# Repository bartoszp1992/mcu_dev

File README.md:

# MCU DEV G071KBT 

- STM32G071KBT 
- 2x 1117 (3V3, 5V)
- kwarc zegarkowy. 
- GPIO
- SWD
- 2x LED (power, GPIO).

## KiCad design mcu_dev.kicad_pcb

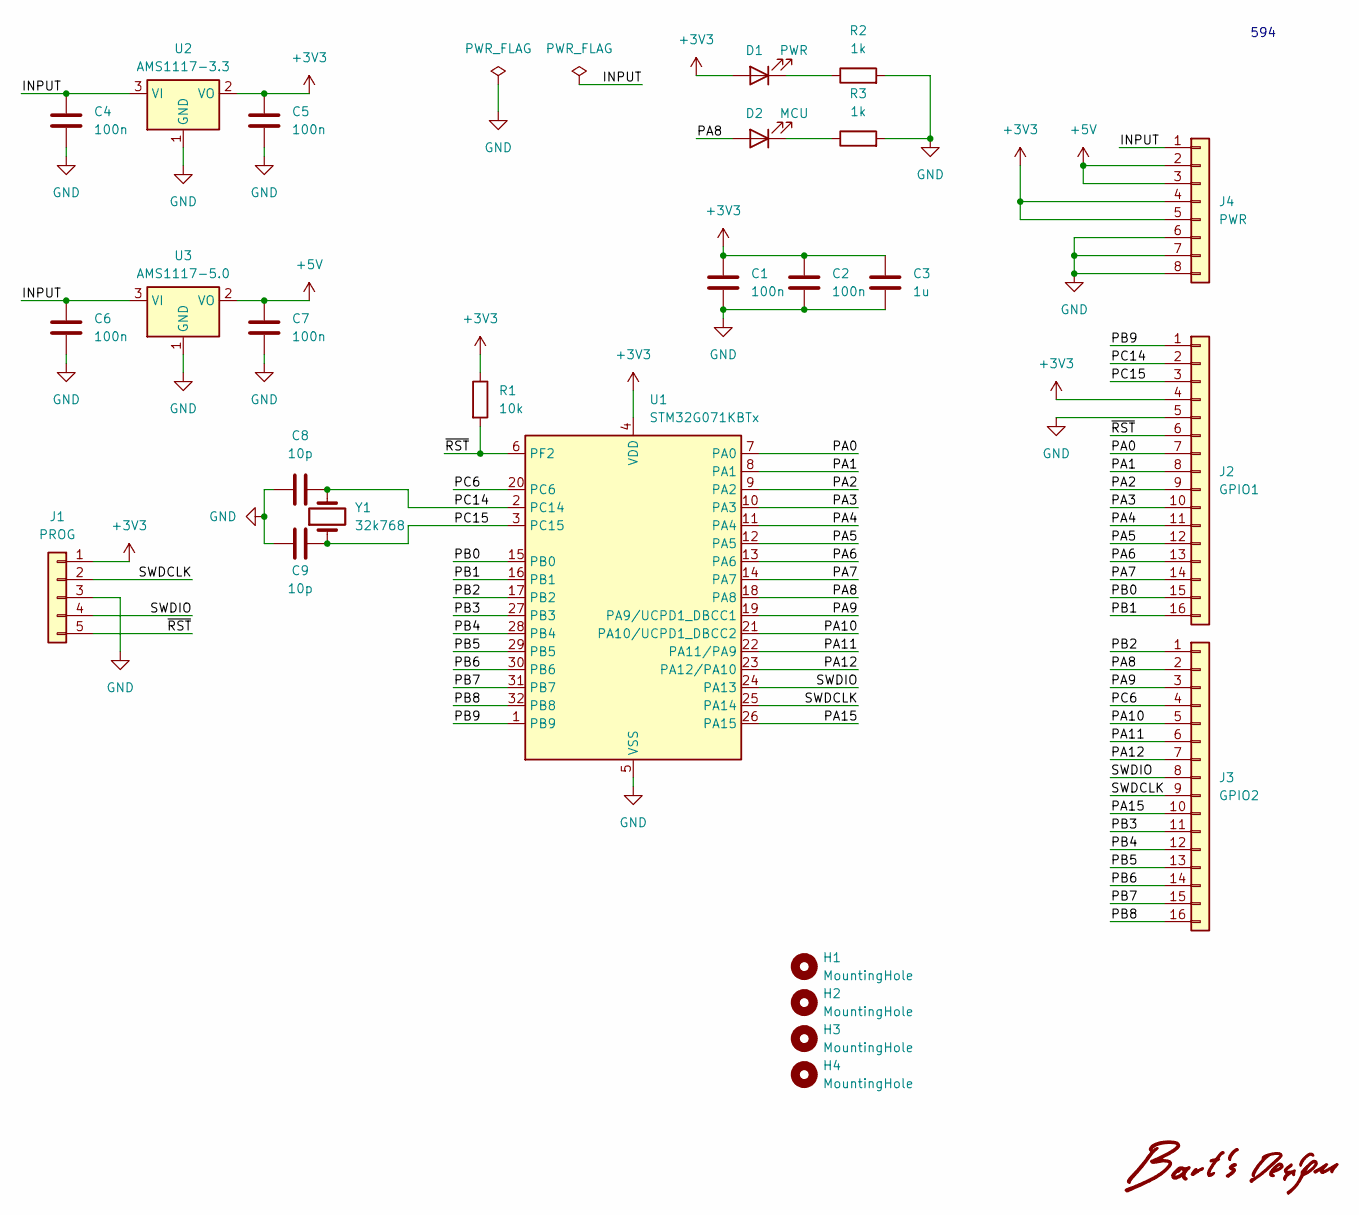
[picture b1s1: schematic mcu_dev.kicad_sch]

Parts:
C1, C2, C4, C5, C6, C7: 100n; C_0603_1608Metric
C3: 1u; C_0603_1608Metric
C8, C9: 10p; C_0603_1608Metric
D1: PWR; LED_0603_1608Metric
D2: MCU; LED_0603_1608Metric
H1, H2, H3, H4: MountingHole; MountingHole_3.2mm_M3
J1: PROG; PinSocket_1x05_P2.54mm_Vertical
J2: GPIO1; PinSocket_1x16_P2.54mm_Vertical
J3: GPIO2; PinSocket_1x16_P2.54mm_Vertical
J4: PWR; PinSocket_1x08_P2.54mm_Vertical
Logo1: Barts Design
R1: 10k; R_0603_1608Metric
R2, R3: 1k; R_0603_1608Metric
U1: STM32G071KBTx; LQFP-32_7x7mm_P0.8mm
U2: AMS1117-3.3; SOT-223-3_TabPin2
U3: AMS1117-5.0; SOT-223-3_TabPin2
Y1: 32k768; Crystal_AT310_D3.0mm_L10.0mm_Horizontal

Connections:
+3V3: C1.1, C2.1, C3.1, C5.1, D1.2 (A), J1.1, J2.4, J4.4, J4.5, R1.1, U1.4 (VDD), U2.2 (VO)
+5V: C7.1, J4.2, J4.3, U3.2 (VO)
/INPUT: C4.1, C6.1, J4.1, U2.3 (VI), U3.3 (VI)
/PA0: J2.7, U1.7 (PA0)
/PA1: J2.8, U1.8 (PA1)
/PA2: J2.9, U1.9 (PA2)
/PA3: J2.10, U1.10 (PA3)
/PA4: J2.11, U1.11 (PA4)
/PA5: J2.12, U1.12 (PA5)
/PA6: J2.13, U1.13 (PA6)
/PA7: J2.14, U1.14 (PA7)
/PA8: D2.2 (A), J3.2, U1.18 (PA8)
/PA9: J3.3, U1.19 (PA9/UCPD1_DBCC1)
/PA10: J3.5, U1.21 (PA10/UCPD1_DBCC2)
/PA11: J3.6, U1.22 (PA11/PA9)
/PA12: J3.7, U1.23 (PA12/PA10)
/PA15: J3.10, U1.26 (PA15)
/PB0: J2.15, U1.15 (PB0)
/PB1: J2.16, U1.16 (PB1)
/PB2: J3.1, U1.17 (PB2)
/PB3: J3.11, U1.27 (PB3)
/PB4: J3.12, U1.28 (PB4)
/PB5: J3.13, U1.29 (PB5)
/PB6: J3.14, U1.30 (PB6)
/PB7: J3.15, U1.31 (PB7)
/PB8: J3.16, U1.32 (PB8)
/PB9: J2.1, U1.1 (PB9)
/PC6: J3.4, U1.20 (PC6)
/PC14: C8.2, J2.2, U1.2 (PC14), Y1.2
/PC15: C9.2, J2.3, U1.3 (PC15), Y1.1
/SWDCLK: J1.2, J3.9, U1.25 (PA14)
/SWDIO: J1.4, J3.8, U1.24 (PA13)
/~RST: J1.5, J2.6, R1.2, U1.6 (PF2)
GND: C1.2, C2.2, C3.2, C4.2, C5.2, C6.2, C7.2, C8.1, C9.1, J1.3, J2.5, J4.6, J4.7, J4.8, R2.2, R3.2, U1.5 (VSS), U2.1 (GND), U3.1 (GND)
unnamed: D1.1 (K), R2.1
unnamed: D2.1 (K), R3.1

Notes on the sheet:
594

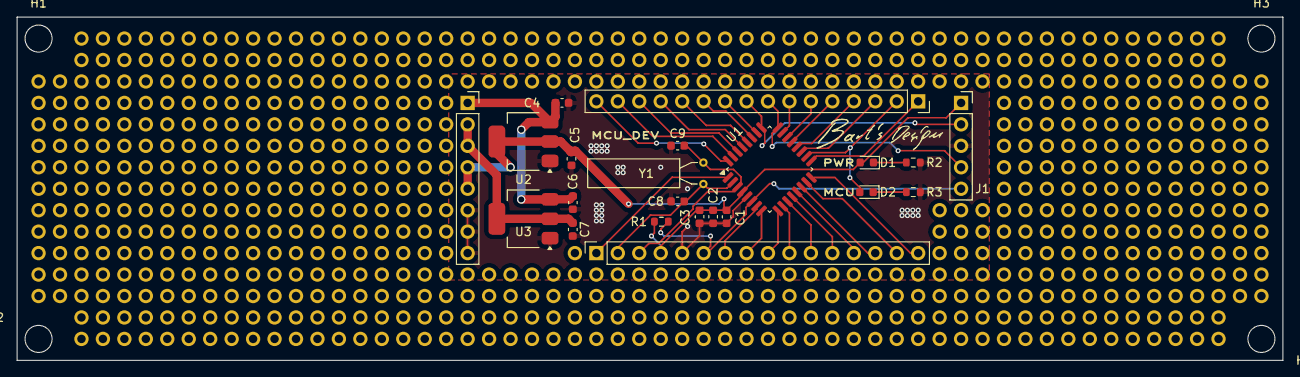
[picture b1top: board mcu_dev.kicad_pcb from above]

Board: 2 copper layers, 149.9 x 40.6 mm, 27 parts (0 on the bottom side), 36 nets.

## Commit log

2024-05-18 initial
2024-05-20 added README with render and schematic
